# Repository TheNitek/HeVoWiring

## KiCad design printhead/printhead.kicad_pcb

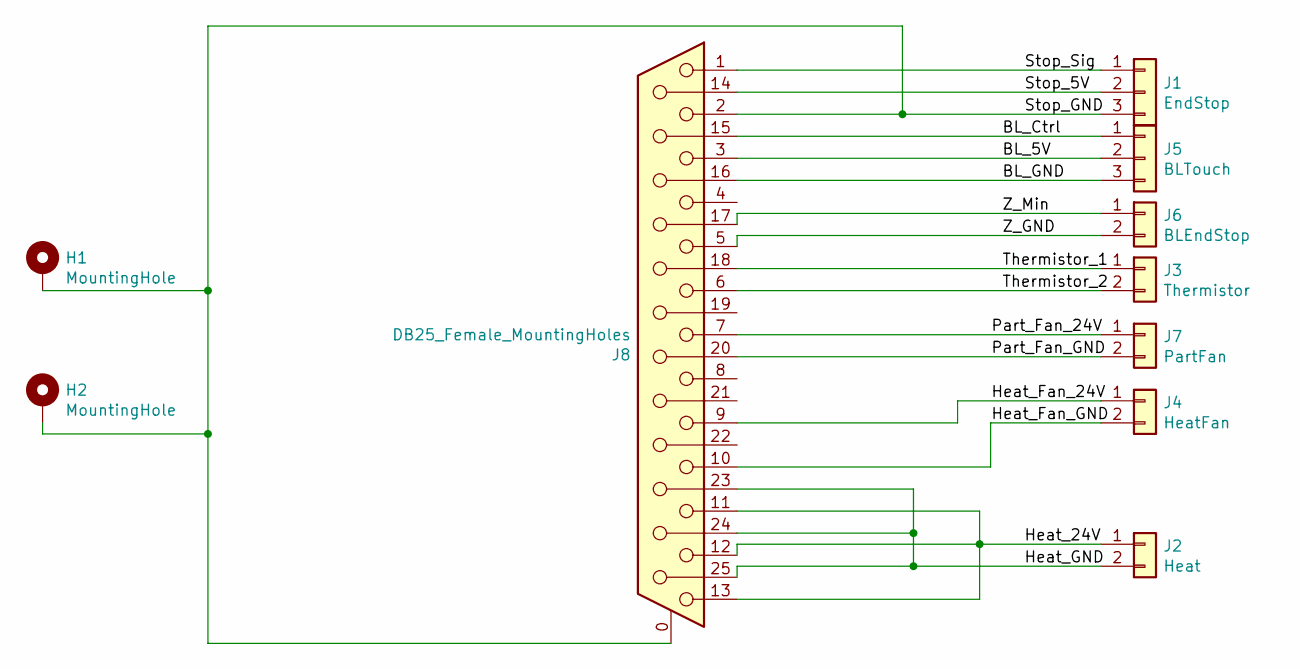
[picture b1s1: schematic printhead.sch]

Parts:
H1, H2: MountingHole; MountingHole_3.2mm_M3_Pad_Via
J1: EndStop; JST_XH_B3B-XH-A_1x03_P2.50mm_Vertical
J2: Heat; JST_XH_B2B-XH-A_1x02_P2.50mm_Vertical
J3: Thermistor; JST_XH_B2B-XH-A_1x02_P2.50mm_Vertical
J4: HeatFan; JST_XH_B2B-XH-A_1x02_P2.50mm_Vertical
J5: BLTouch; JST_XH_B3B-XH-A_1x03_P2.50mm_Vertical
J6: BLEndStop; JST_XH_B2B-XH-A_1x02_P2.50mm_Vertical
J7: PartFan; JST_XH_B2B-XH-A_1x02_P2.50mm_Vertical
J8: DB25_Female_MountingHoles; DSUB-25_Female_Horizontal_P2.77x2.84mm_EdgePinOffset4.94mm_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

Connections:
/BL_5V: J5.2, J8.3
/BL_Ctrl: J5.1, J8.15
/BL_GND: J5.3, J8.16
/Heat_24V: J2.1, J8.11, J8.12, J8.13
/Heat_Fan_24V: J4.1, J8.9
/Heat_Fan_GND: J4.2, J8.10
/Heat_GND: J2.2, J8.23, J8.24, J8.25
/Part_Fan_24V: J7.1, J8.7
/Part_Fan_GND: J7.2, J8.20
/Stop_5V: J1.2, J8.14
/Stop_GND: H1.1, H2.1, J1.3, J8.0 (PAD), J8.2
/Stop_Sig: J1.1, J8.1
/Thermistor_1: J3.1, J8.18
/Thermistor_2: J3.2, J8.6
/Z_GND: J6.2, J8.5
/Z_Min: J6.1, J8.17

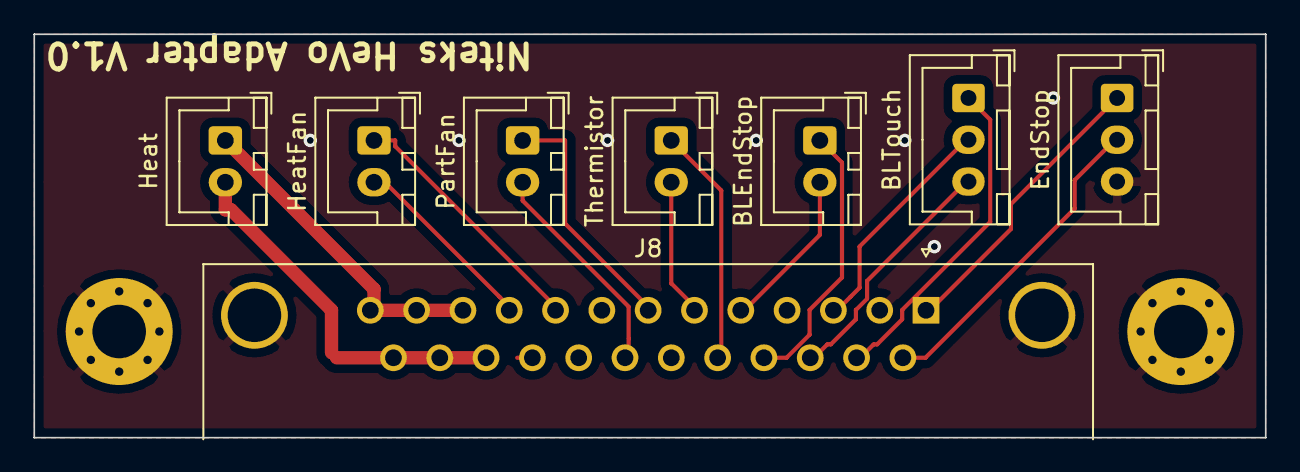
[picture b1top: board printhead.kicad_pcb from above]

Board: 2 copper layers, 73.7 x 24.1 mm, 10 parts (0 on the bottom side), 16 nets.

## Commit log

2019-06-16 V1.0
